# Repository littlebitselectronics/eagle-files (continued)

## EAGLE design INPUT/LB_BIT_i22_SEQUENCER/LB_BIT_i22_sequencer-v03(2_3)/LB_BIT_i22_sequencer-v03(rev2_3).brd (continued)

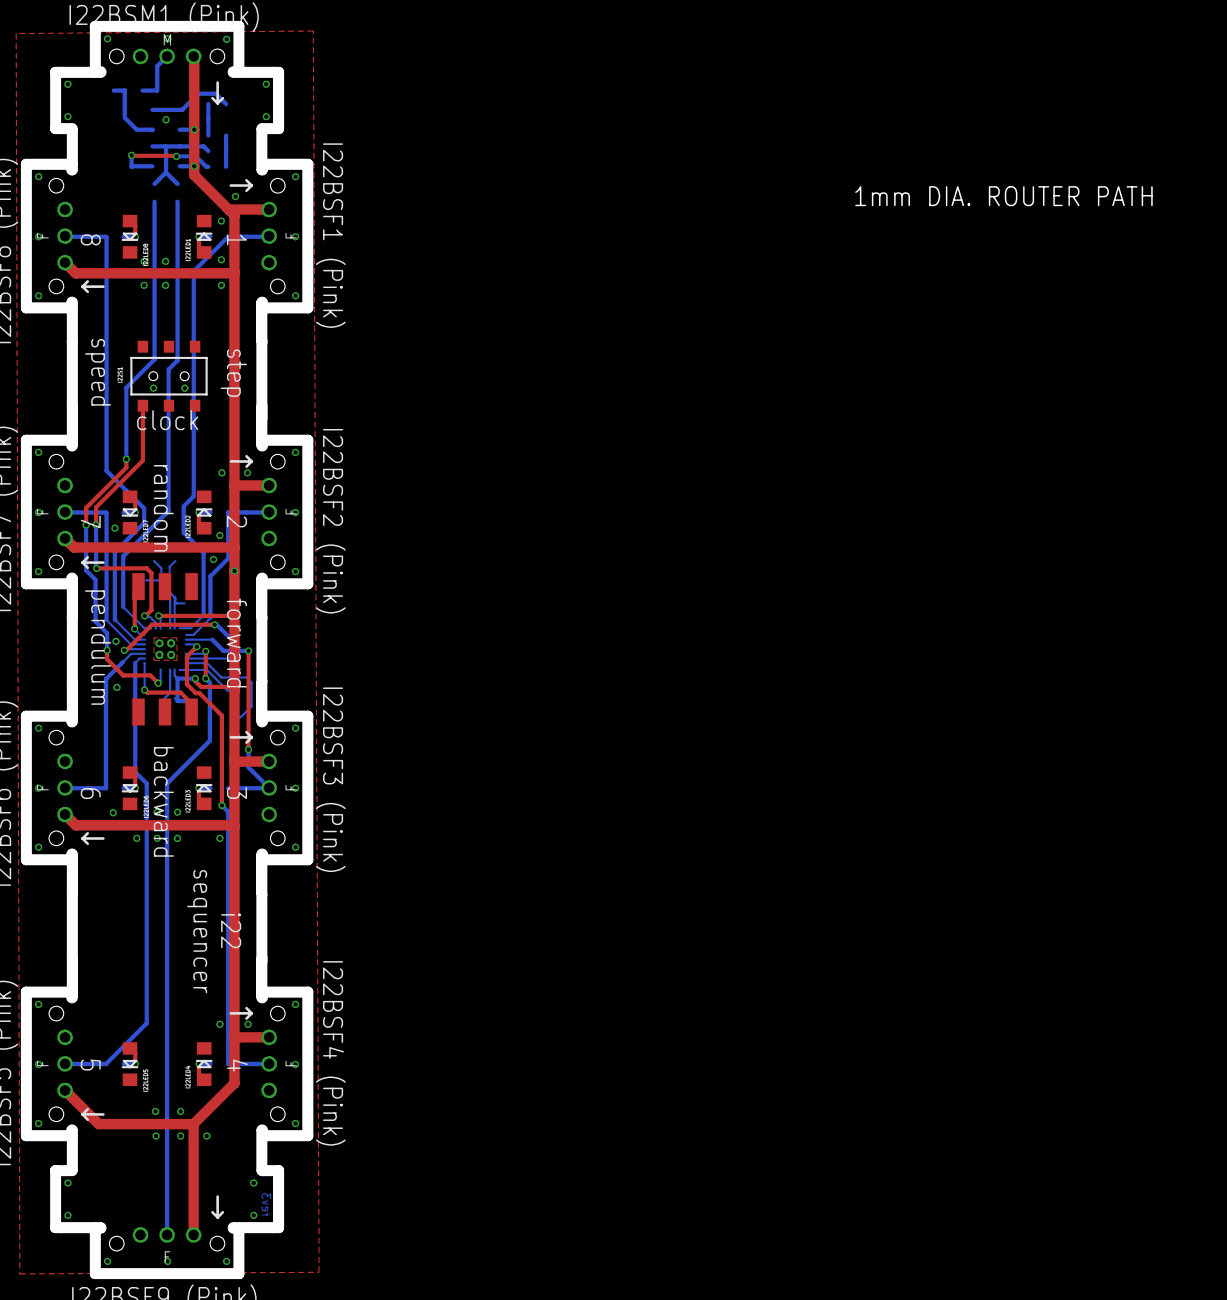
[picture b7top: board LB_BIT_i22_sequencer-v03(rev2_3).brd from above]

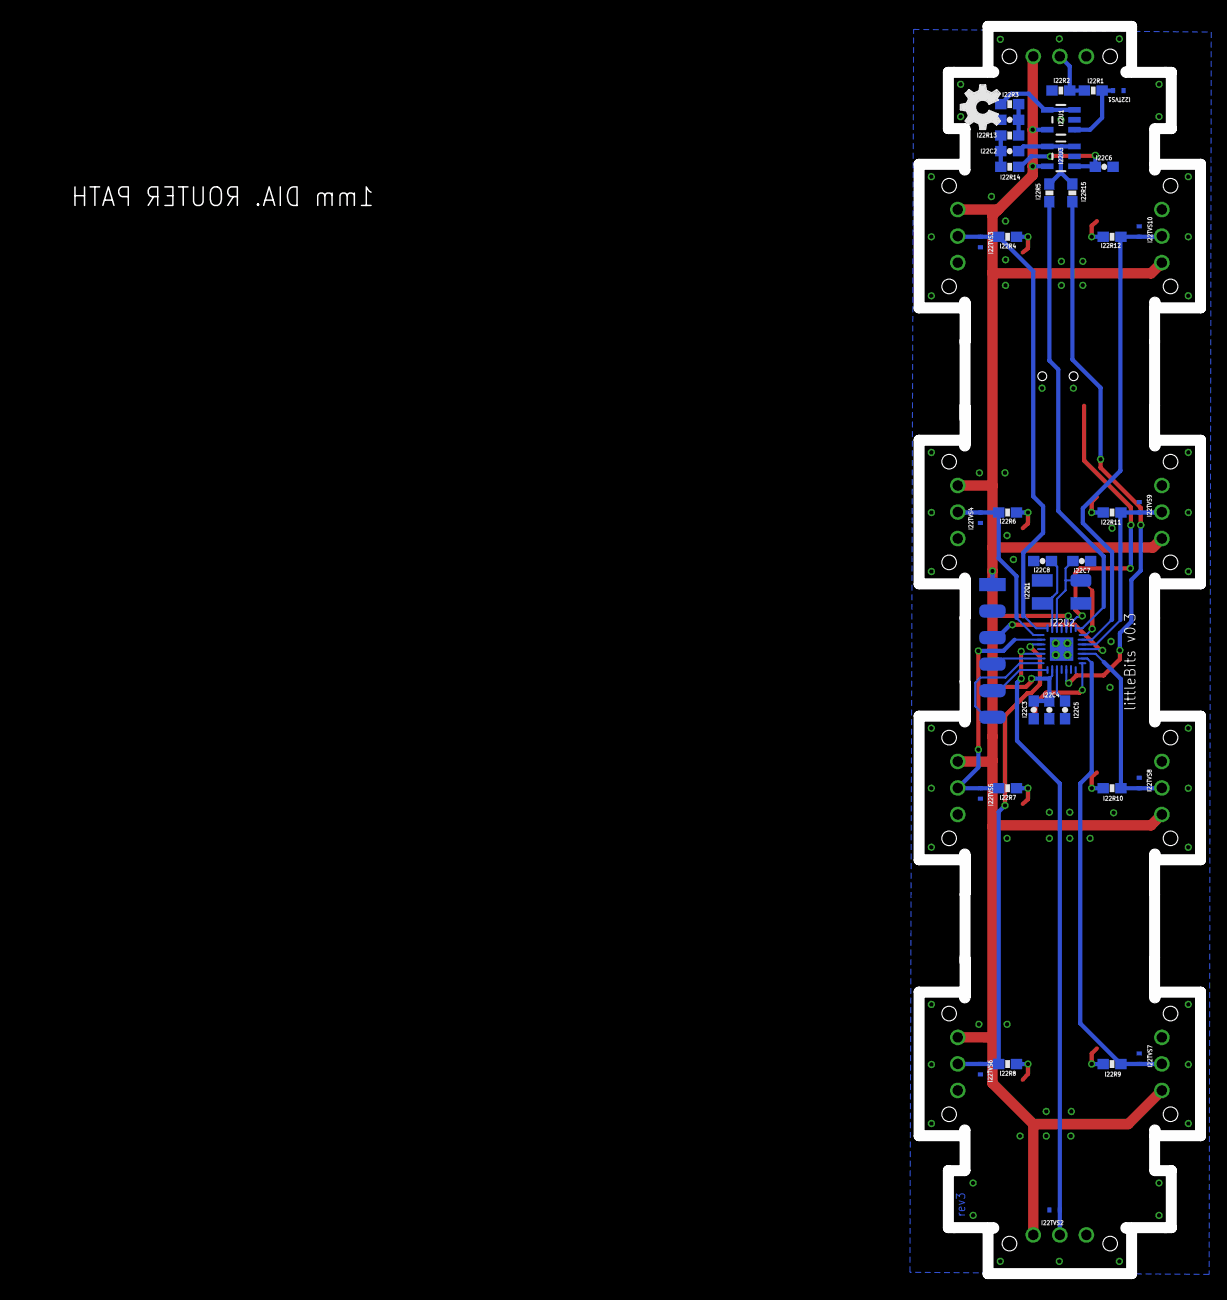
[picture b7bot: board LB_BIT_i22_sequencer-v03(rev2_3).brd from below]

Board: 2 copper layers, 27.0 x 119.5 mm, 62 parts (38 on the bottom side), 38 nets.

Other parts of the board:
U$12: OSHW_FILLX150_NOTEXT
